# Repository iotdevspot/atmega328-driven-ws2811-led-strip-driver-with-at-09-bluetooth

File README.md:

# atmega328-driven-ws2811-led-strip-driver-with-at-09-bluetooth

This project contains a WS2811 LED strip driver hardware with 2 different communication modes with appropirate Arduino sketches for each. 

The two communication modes are the following:

* **WiFi** supported by an ESP8266 Wifi module
* **BLE** supported by an AT-09 Bluetooth module

## Bluetooth version

I've used the following AT commands in order to change the behaviour (changing name, changing pin and the baud rate) of the BLE module and I've done them before attaching it to the board. 

* AT+NAME
* AT+PIN
* AT+BAUD

After this procedure the module is ready to be assembled.

**Useable commands and their descriptions in the following format: "command" - description**
* "A" - Red color mode
* "B" - Green color mode
* "C" - Blue color mode
* "D" - Rainbow 1 mode
* "E" - Rainbow 2 mode
* "F" - Custom color mode
* "G,<color red 0..255>,<color green 0..255>,<color blue 0..255>" - Color setting command
* "H" - Relay on command
* "I" - Relay off command

## WiFi version

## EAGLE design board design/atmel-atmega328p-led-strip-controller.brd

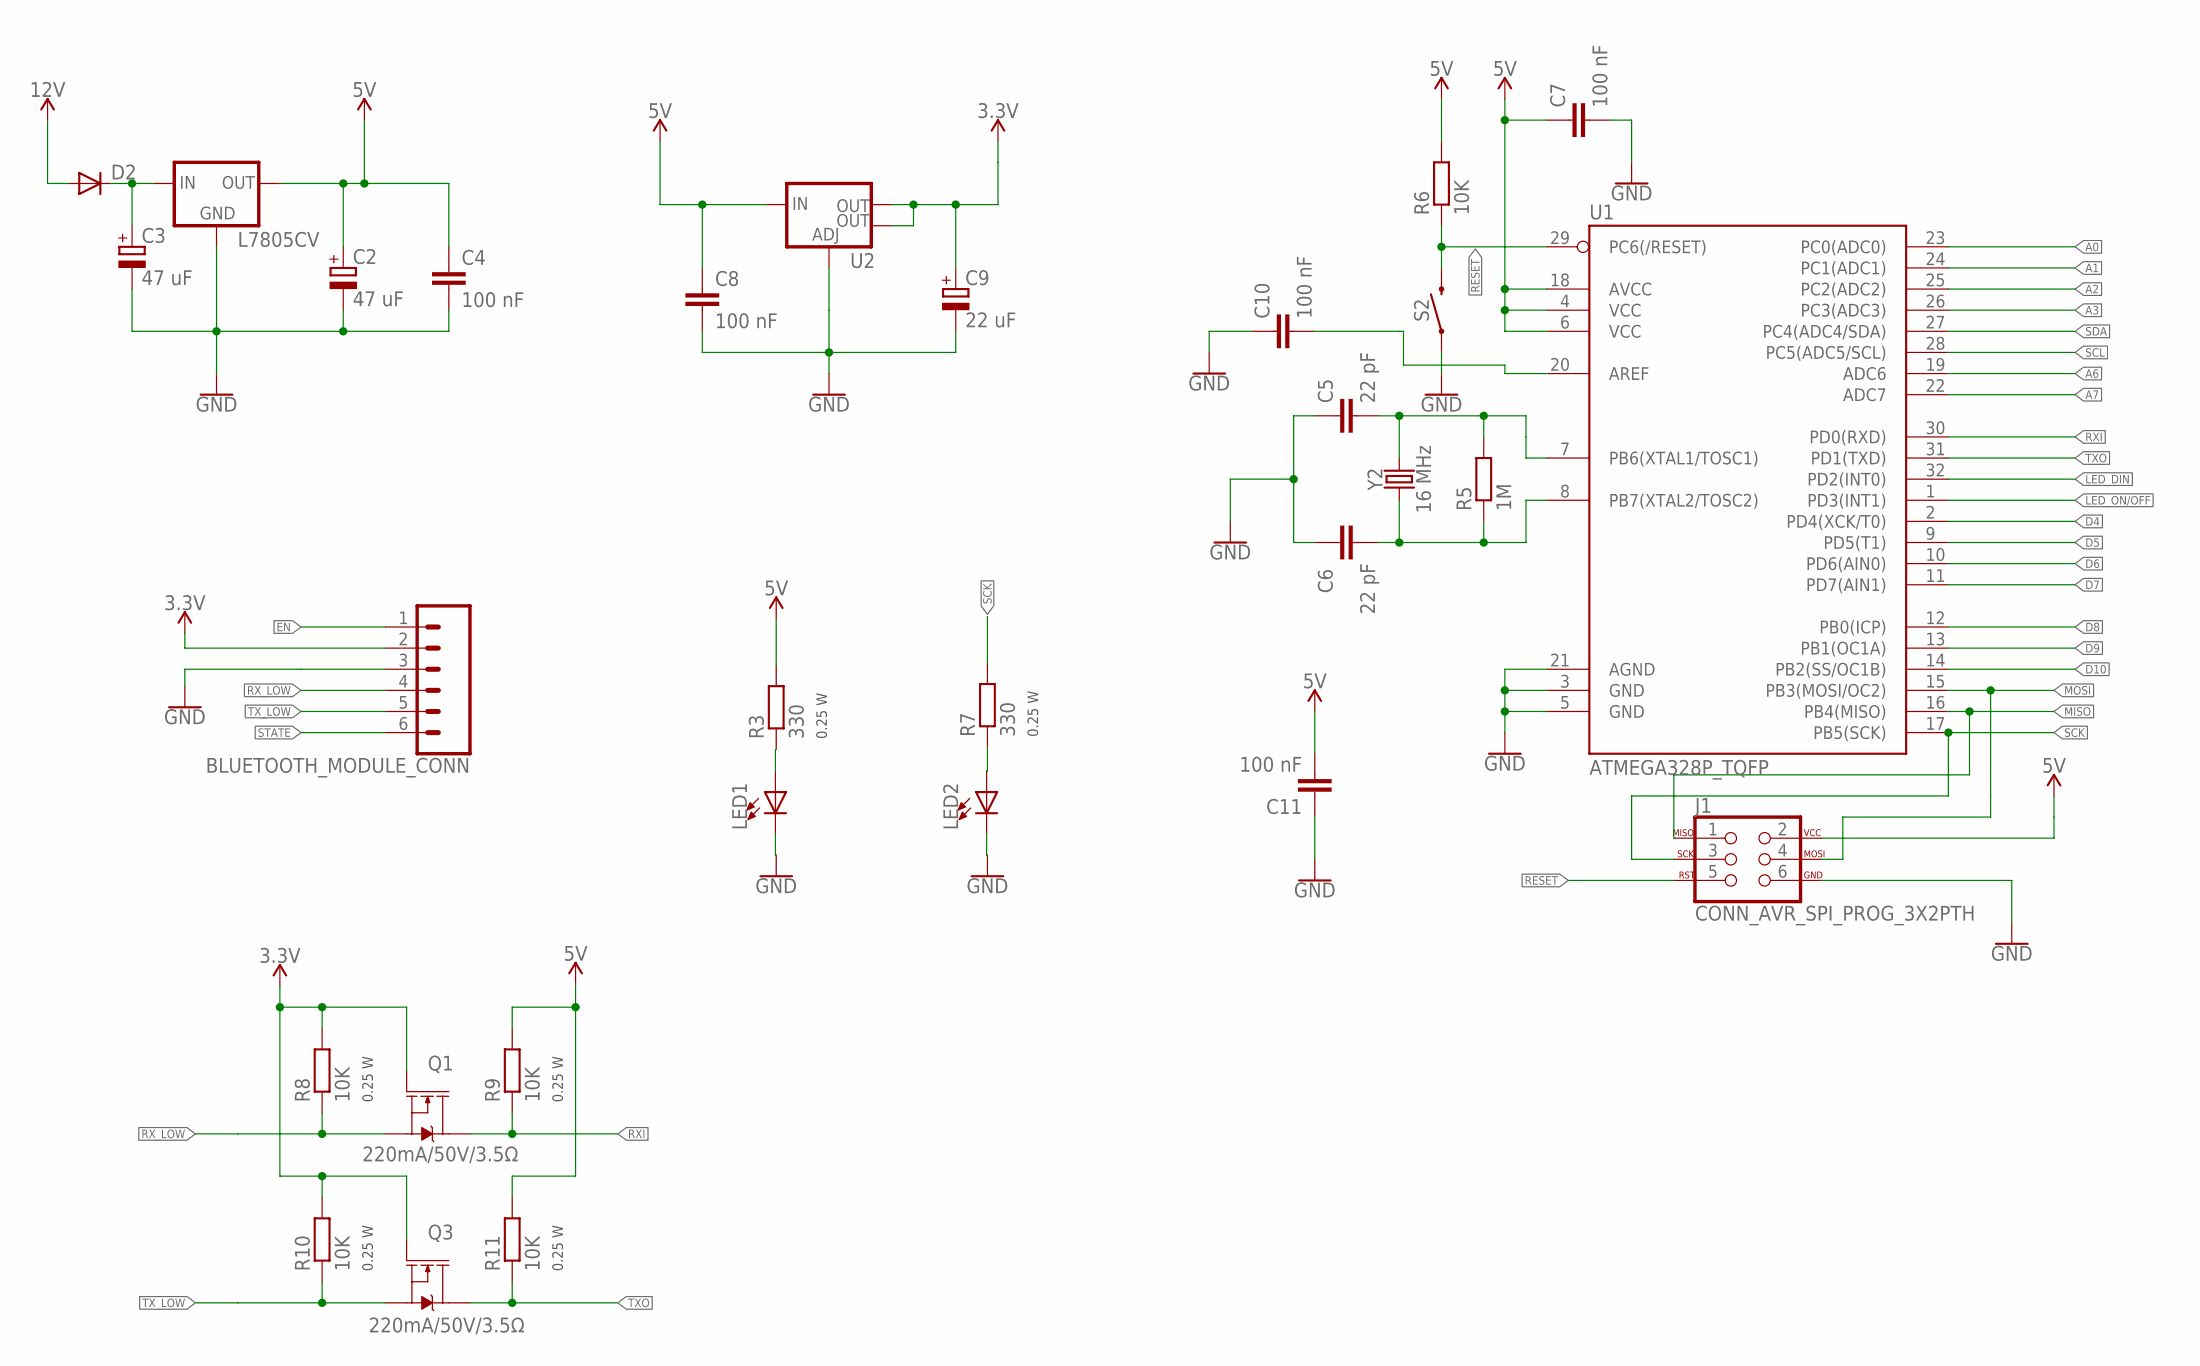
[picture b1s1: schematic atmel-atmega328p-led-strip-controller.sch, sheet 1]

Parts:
BLUETOOTH_MODULE_CONN: CONN_06SILK_FEMALE_PTH; 1X06
C2, C3: 47 uF; E2,5-5
C4, C7, C8, C10, C11: 100 nF; C1206I-C3216M
C5, C6: 22 pF; C1206I-C3216M
C9: 22 uF; 153CLV-0505
D2: DIODED-10; D-10
J1: CONN_AVR_SPI_PROG_3X2PTH; 2X3_S
L7805CV: V_REG_78XX_STANDING; 78XXS
LED1, LED2: LEDCHIPLED_1206_G; LED_1206_G
Q1, Q3: 220mA/50V/3.5Ω; SOT23-3
R3, R7: 330; R1206
R5: 1M; R1206
R6, R8, R9, R10, R11: 10K; R1206
S2: INPUT_MOMENTARY_SWITCH_SPST-SMD-5.2MM; TACTILE_SWITCH_SMD_5.2MM
U1: ATMEGA328P_TQFP; TQFP32-08
U2: V_REG_LM1117SOT223; SOT223
Y2: 16 MHz; CRYSTAL-SMD-3.2X2.5MM

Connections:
3.3V: BLUETOOTH_MODULE_CONN.2, C9.+, Q1.1 (G), Q3.1 (G), R8.2, R10.2, U2.2 (OUT), U2.4 (OUT)
5V: C2.+, C4.1, C7.1, C8.1, C11.2, J1.2, L7805CV.OUT, R3.2, R6.2, R9.2, R11.2, U1.4 (VCC), U1.6 (VCC), U1.18 (AVCC), U2.3 (IN); also elsewhere on the board
12V: D2.A; also elsewhere on the board
A0: U1.23 (PC0(ADC0))
A1: U1.24 (PC1(ADC1))
A2: U1.25 (PC2(ADC2))
A3: U1.26 (PC3(ADC3))
A6: U1.19 (ADC6)
A7: U1.22 (ADC7)
D4: U1.2 (PD4(XCK/T0))
D5: U1.9 (PD5(T1))
D6: U1.10 (PD6(AIN0))
D7: U1.11 (PD7(AIN1))
D8: U1.12 (PB0(ICP))
D9: U1.13 (PB1(OC1A))
D10: U1.14 (PB2(SS/OC1B))
EN: BLUETOOTH_MODULE_CONN.1
GND: BLUETOOTH_MODULE_CONN.3, C2.-, C3.-, C4.2, C5.1, C6.1, C7.2, C8.2, C9.-, C10.1, C11.1, J1.6, L7805CV.GND, LED1.C, LED2.C, S2.1, U1.3 (GND), U1.5 (GND), U1.21 (AGND), U2.1 (ADJ); also elsewhere on the board
LED_DIN: U1.32 (PD2(INT0)); also elsewhere on the board
LED_ON/OFF: U1.1 (PD3(INT1)); also elsewhere on the board
MISO: J1.1, U1.16 (PB4(MISO))
MOSI: J1.4, U1.15 (PB3(MOSI/OC2))
unnamed: C5.2, R5.2, U1.7 (PB6(XTAL1/TOSC1)), Y2.3 (2)
unnamed: C6.2, R5.1, U1.8 (PB7(XTAL2/TOSC2)), Y2.1
unnamed: C10.2, U1.20 (AREF)
unnamed: LED1.A, R3.1
unnamed: C3.+, D2.C, L7805CV.IN
unnamed: LED2.A, R7.1
RESET: J1.5, R6.1, S2.3 (2), U1.29 (PC6(/RESET))
RXI: Q1.3 (D), R9.1, U1.30 (PD0(RXD))
RX_LOW: BLUETOOTH_MODULE_CONN.4, Q1.2 (S), R8.1
SCK: J1.3, R7.2, U1.17 (PB5(SCK))
SCL: U1.28 (PC5(ADC5/SCL))
SDA: U1.27 (PC4(ADC4/SDA))
STATE: BLUETOOTH_MODULE_CONN.6
TXO: Q3.3 (D), R11.1, U1.31 (PD1(TXD))
TX_LOW: BLUETOOTH_MODULE_CONN.5, Q3.2 (S), R10.1

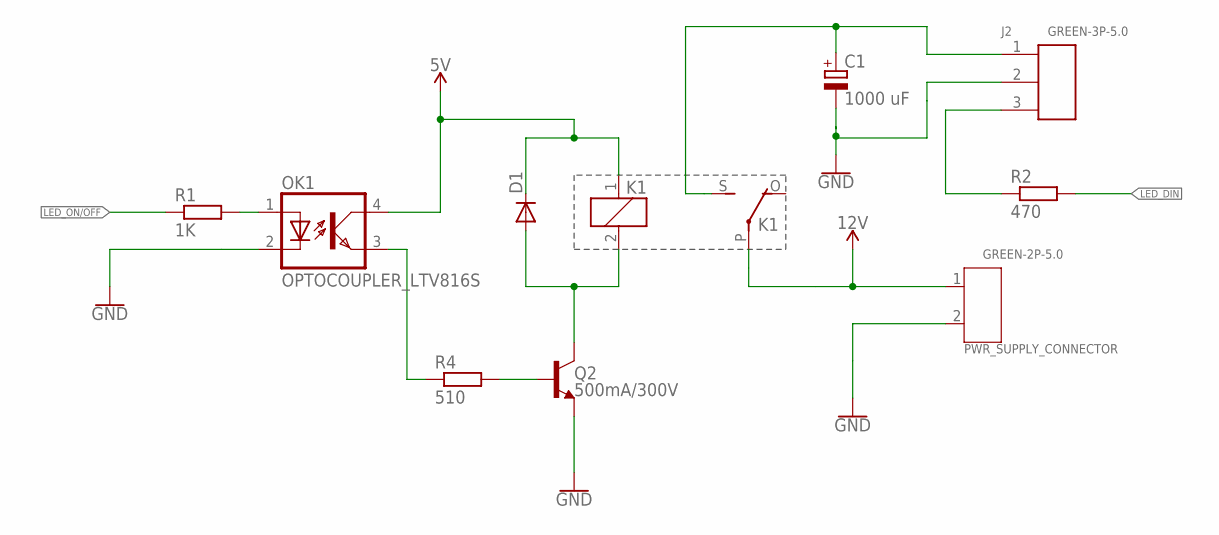
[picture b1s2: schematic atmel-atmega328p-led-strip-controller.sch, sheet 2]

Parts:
C1: 1000 uF; E5-13
D1: DIODED-10; D-10
J2: GREEN-3P-5.0; H3-5.0-15.5X8.0MM
K1: RELAY_ZF112; ZF112
OK1: OPTOCOUPLER_LTV816S; DIL4-SMD
PWR_SUPPLY_CONNECTOR: GREEN-2P-5.0; H2-5.0-10.5X8.0MM
Q2: 500mA/300V; SOT23-3
R1: 1K; R1206
R2: 470; R1206
R4: 510; R1206

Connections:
5V: D1.C, K1.1, OK1.4 (COL); also elsewhere on the board
12V: K1.P, PWR_SUPPLY_CONNECTOR.1; also elsewhere on the board
GND: C1.-, J2.2, OK1.2 (C), PWR_SUPPLY_CONNECTOR.2, Q2.2 (E); also elsewhere on the board
LED_DIN: R2.2; also elsewhere on the board
LED_ON/OFF: R1.1; also elsewhere on the board
unnamed: J2.3, R2.1
unnamed: D1.A, K1.2, Q2.3 (C)
unnamed: OK1.1 (A), R1.2
unnamed: Q2.1 (B), R4.2
unnamed: OK1.3 (EMIT), R4.1
unnamed: C1.+, J2.1, K1.S

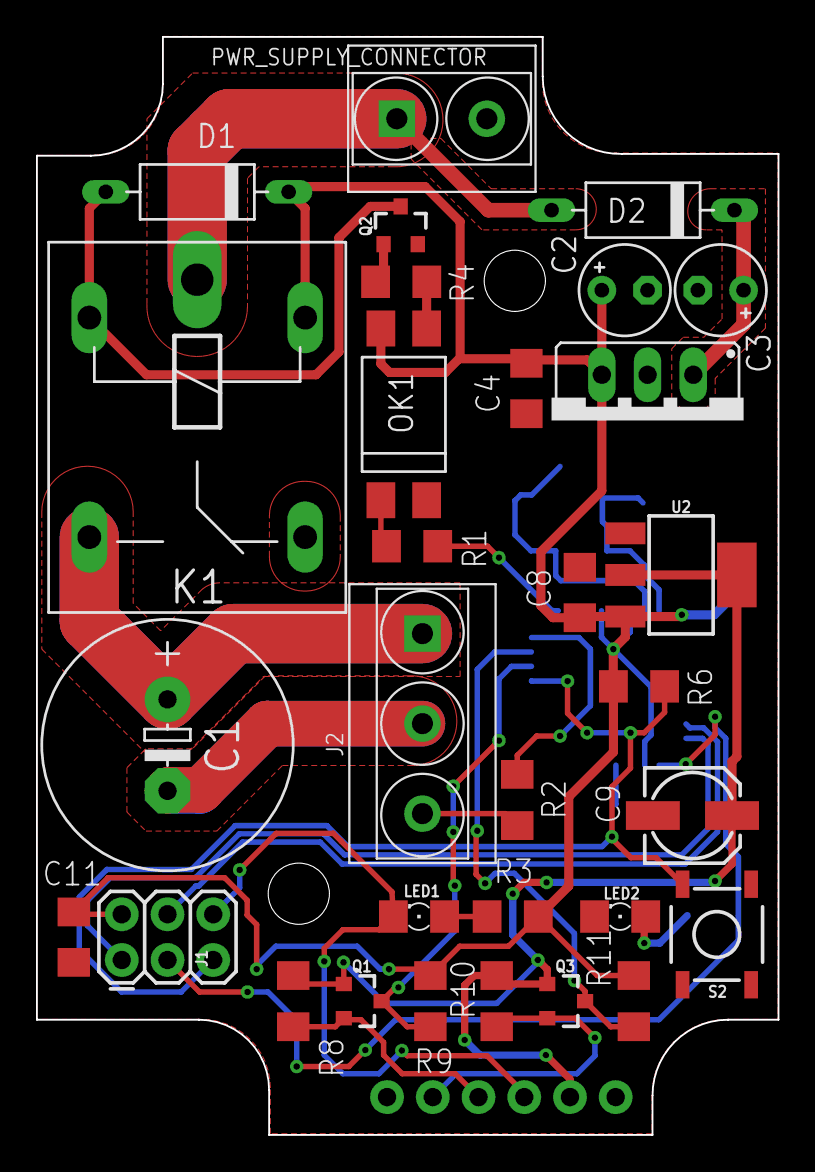
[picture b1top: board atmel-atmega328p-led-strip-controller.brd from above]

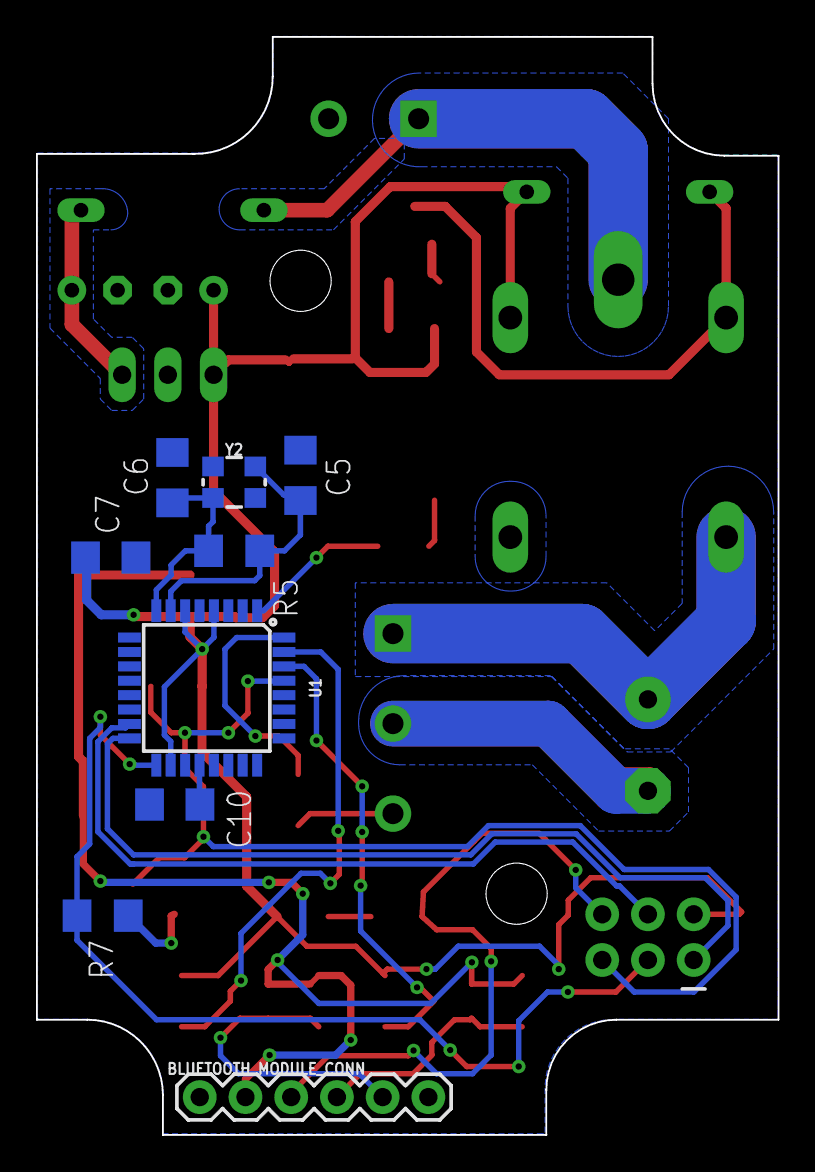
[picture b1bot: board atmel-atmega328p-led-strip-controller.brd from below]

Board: 2 copper layers, 41.2 x 61.0 mm, 40 parts (9 on the bottom side), 26 nets.

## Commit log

2018-11-01 Images, BLE Arduino sketch, tester sketch, board design added

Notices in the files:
parts and their libraries:
SparkFun-PowerSymbols: Licensing: Creative Commons ShareAlike 4.0 International - https://creativecommons.org/licenses/by-sa/4.0
